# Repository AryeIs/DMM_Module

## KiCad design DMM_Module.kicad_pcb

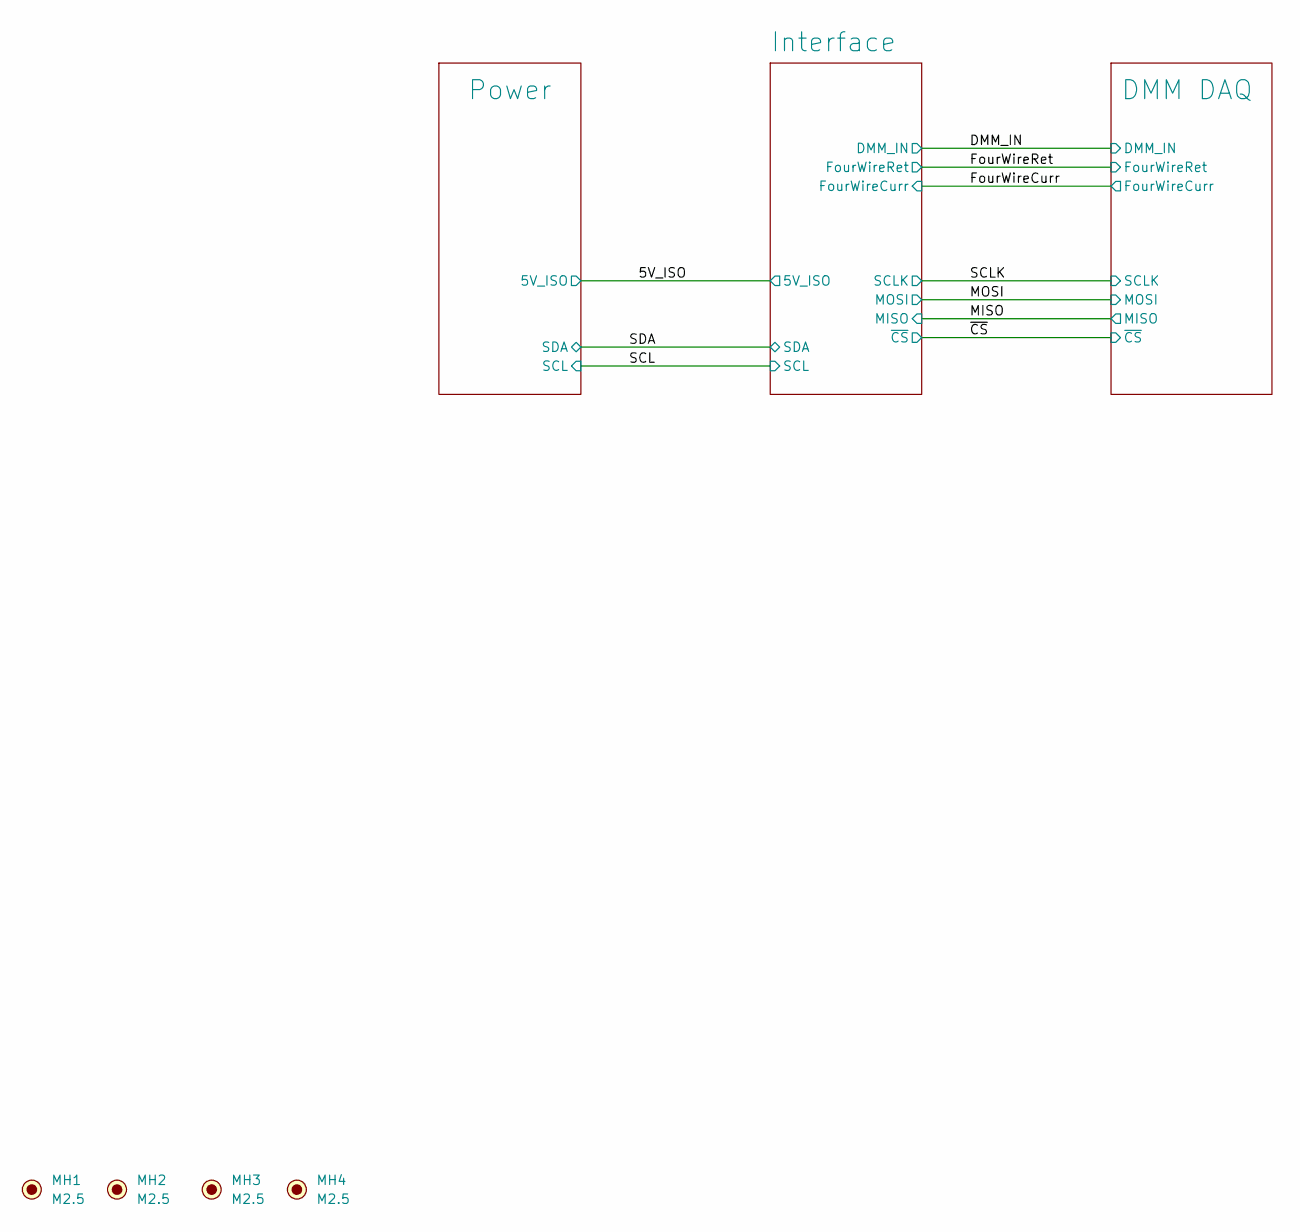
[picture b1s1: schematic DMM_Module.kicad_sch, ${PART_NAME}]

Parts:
MH1, MH2, MH3, MH4: M2.5; MountingHole_2.7mm_M2.5

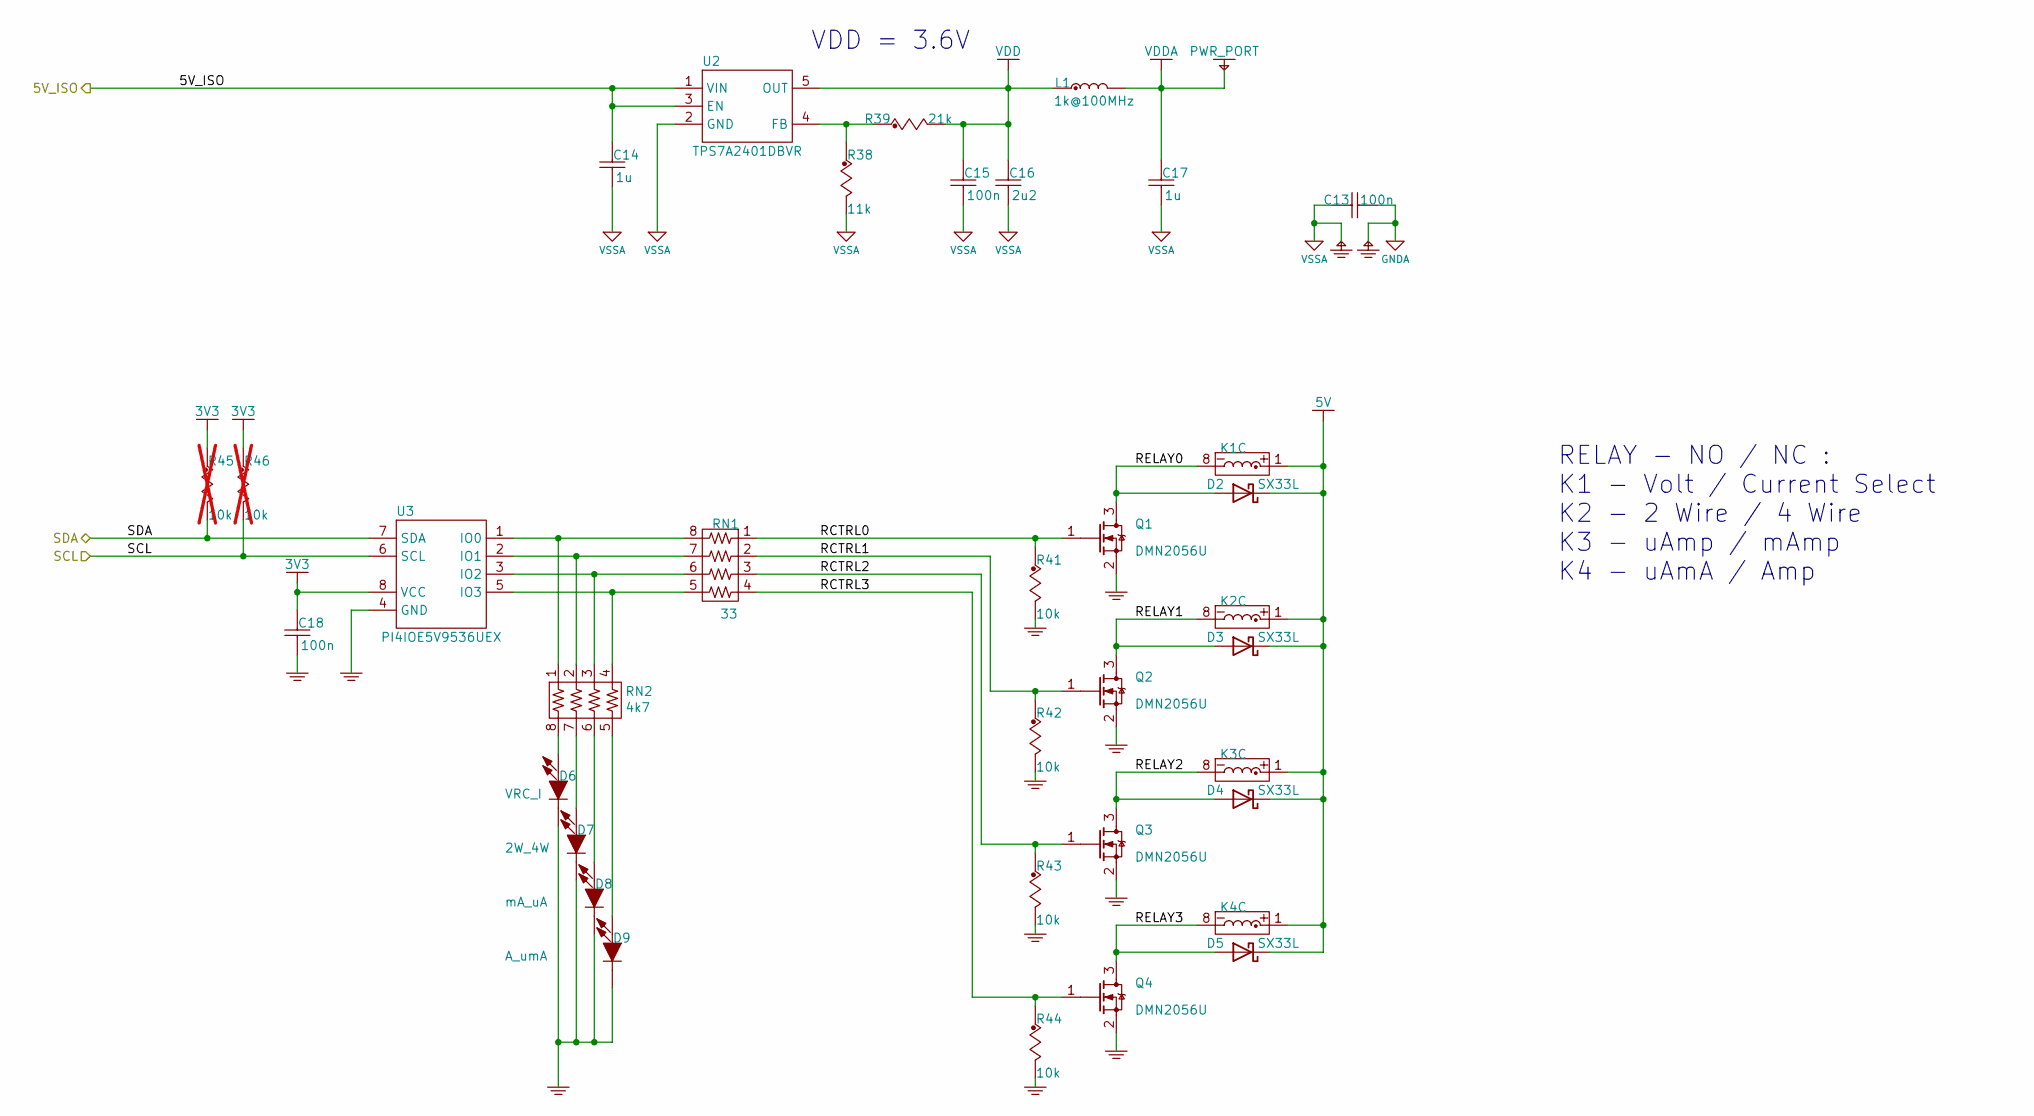
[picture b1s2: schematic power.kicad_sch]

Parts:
C13, C15, C18: 100n; C_0603_1608Metric; Voltage 50V; MFG PN CL10B104JB8NNNC
C14, C17: 1u; C_0603_1608Metric; Voltage 25V; MFG PN CL10B105KA8NNNC
C16: 2u2; C_0603_1608Metric; Voltage 25V; MFG PN CL10A225KP8NNNC
D2, D3, D4, D5: SX33L; D_SOD-123; MFG PN MBR1020VL_R1_00001
D6: VRC_I; LED_0603_1608Metric; MFG PN 150060GS55040
D7: 2W_4W; LED_0603_1608Metric; MFG PN 150060GS55040
D8: mA_uA; LED_0603_1608Metric; MFG PN 150060GS55040
D9: A_umA; LED_0603_1608Metric; MFG PN 150060GS55040
K1, K2, K3, K4: G6K-2F-Y-TR; DPDT_G6K-2F-Y; Voltage 5VDC; MFG PN G6K-2F-Y-TR DC5
L1: 1k@100MHz; L_0603_1608Metric; MFG PN 74279266
Q1, Q2, Q3, Q4: DMN2056U; SOT-23; MFG PN DMN2056U-7
R38: 11k; R_0603_1608Metric; Tolerance 1%; MFG PN CR0603-FX-1102ELF
R39: 21k; R_0603_1608Metric; Tolerance 1%; MFG PN CR0603-FX-2102ELF
R41, R42, R43, R44: 10k; R_0603_1608Metric; Tolerance 1%; MFG PN CR0603AFX-1002EAS
R45, R46: 10k; R_0603_1608Metric; Tolerance 1%; MFG PN CR0603AFX-1002EAS; not fitted
RN1: 33; R_Array_Convex_4x0603; MFG PN YC164-FR-0733RL
RN2: 4k7; R_Array_Convex_4x0603; MFG PN YC164-FR-074K7L
U2: TPS7A2401DBVR; SOT-23-5; MFG PN TPS7A2401DBVR
U3: PI4IOE5V9536UEX; TSSOP-8_3x3mm_P0.65mm; MFG PN PI4IOE5V9536UEX

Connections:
3V3: C18.2, R45.1, R46.1, U3.8 (VCC); also elsewhere on the board
5V: D2.1 (K), D3.1 (K), D4.1 (K), D5.1 (K), K1.1 (COIL1), K2.1 (COIL1), K3.1 (COIL1), K4.1 (COIL1); also elsewhere on the board
/5V_ISO: C14.2, U2.1 (VIN), U2.3 (EN); also elsewhere on the board
/Power/RCTRL0: Q1.1 (G), R41.1, RN1.1
/Power/RCTRL1: Q2.1 (G), R42.1, RN1.2
/Power/RCTRL2: Q3.1 (G), R43.1, RN1.3
/Power/RCTRL3: Q4.1 (G), R44.1, RN1.4
/Power/RELAY0: D2.2 (A), K1.8 (COIL2), Q1.3 (D)
/Power/RELAY1: D3.2 (A), K2.8 (COIL2), Q2.3 (D)
/Power/RELAY2: D4.2 (A), K3.8 (COIL2), Q3.3 (D)
/Power/RELAY3: D5.2 (A), K4.8 (COIL2), Q4.3 (D)
/SCL: R46.2, U3.6 (SCL); also elsewhere on the board
/SDA: R45.2, U3.7 (SDA); also elsewhere on the board
GND: C18.1, D6.1 (K), D7.1 (K), D8.1 (K), D9.1 (K), Q1.2 (S), Q2.2 (S), Q3.2 (S), Q4.2 (S), R41.2, R42.2, R43.2, R44.2, U3.4 (GND); also elsewhere on the board
unnamed: D6.2 (A), RN2.8
unnamed: D7.2 (A), RN2.7
unnamed: D8.2 (A), RN2.6
unnamed: D9.2 (A), RN2.5
unnamed: R38.1, R39.1, U2.4 (FB)
unnamed: RN1.8, RN2.1, U3.1 (IO0)
unnamed: RN1.7, RN2.2, U3.2 (IO1)
unnamed: RN1.6, RN2.3, U3.3 (IO2)
unnamed: RN1.5, RN2.4, U3.5 (IO3)
VDD: C15.2, C16.2, L1.1, R39.2, U2.5 (OUT); also elsewhere on the board
VDDA: C17.2, L1.2; also elsewhere on the board

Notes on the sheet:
RELAY - NO / NC : K1 - Volt / Current Select K2 - 2 Wire / 4 Wire K3 - uAmp / mAmp K4 - uAmA / Amp
VDD = 3.6V

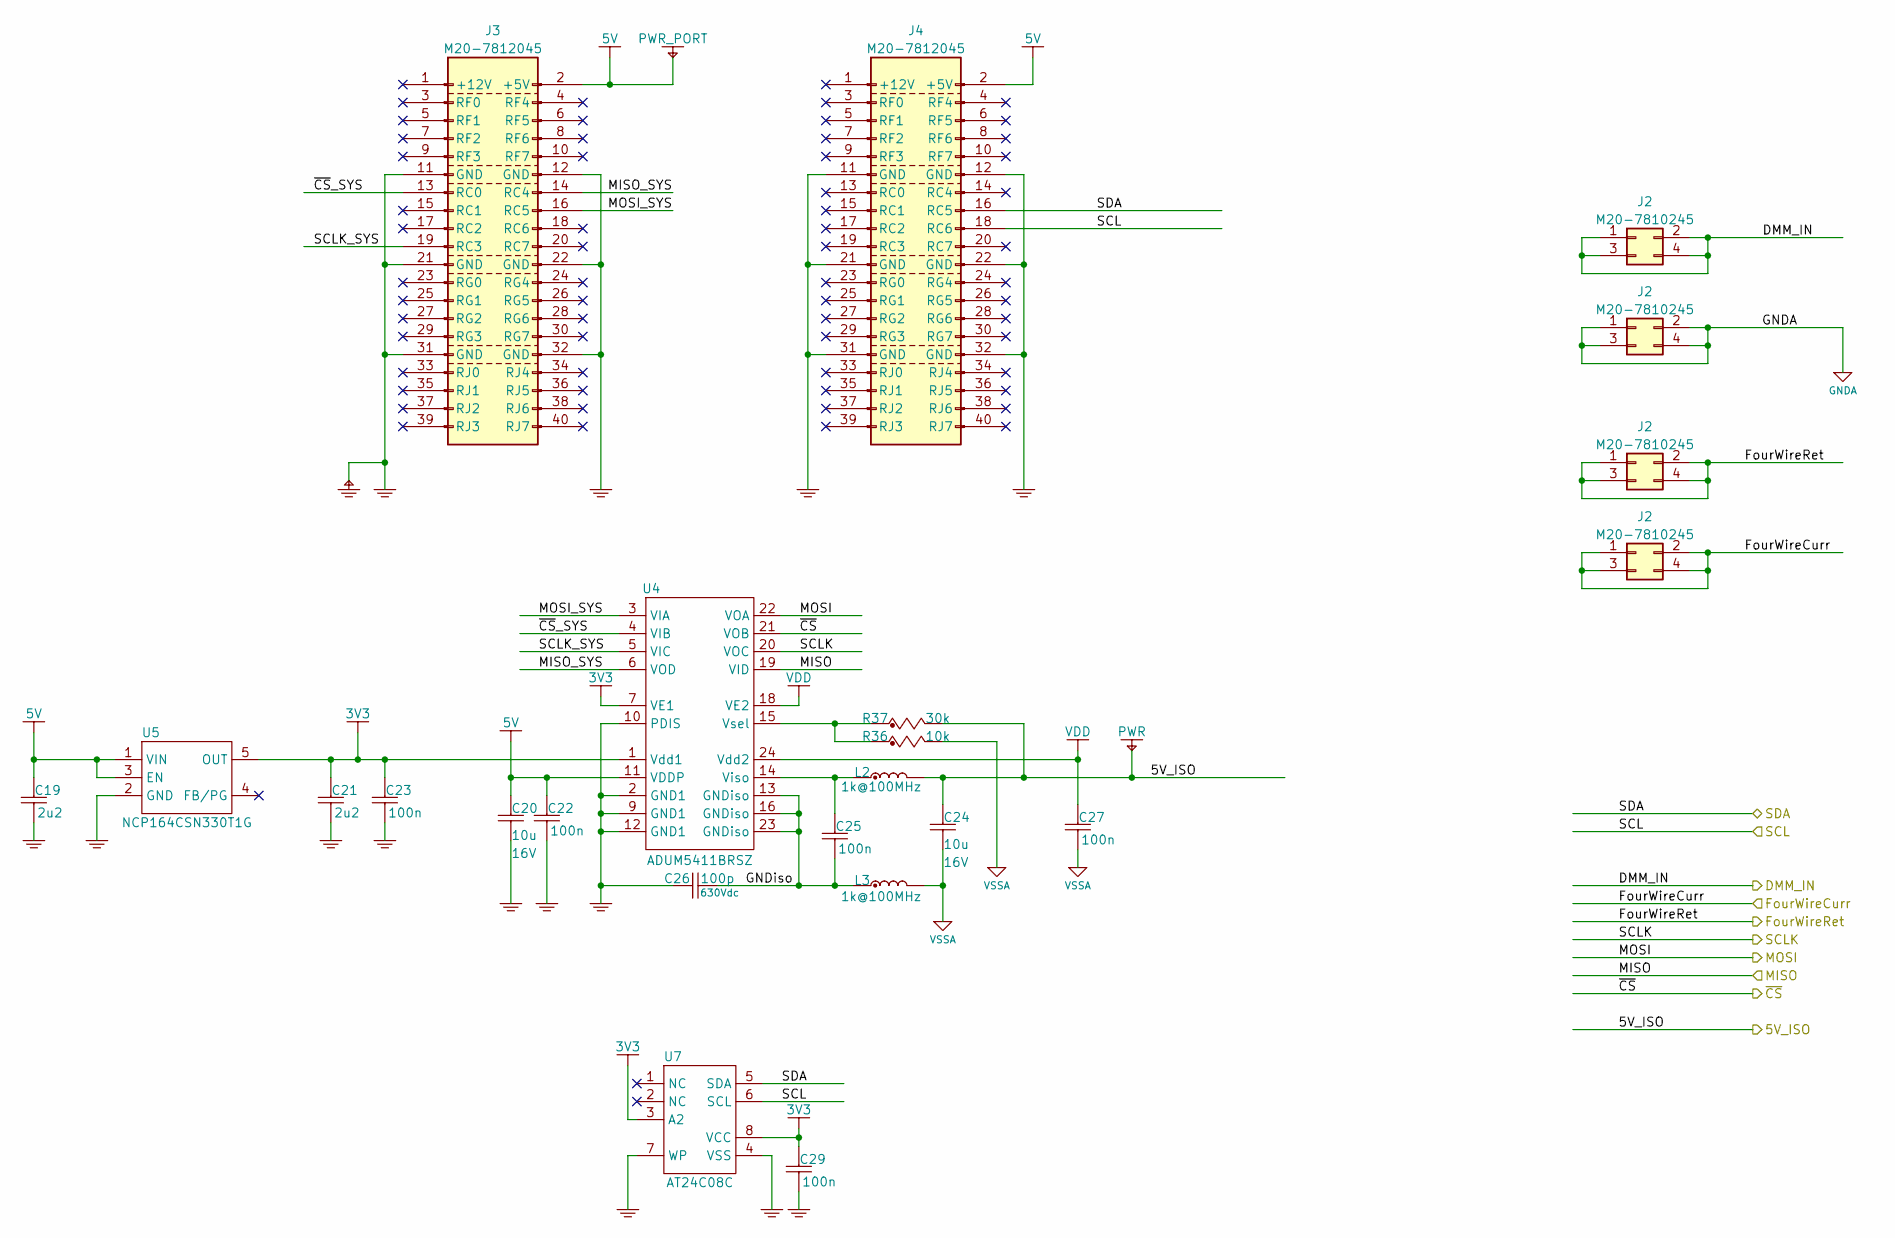
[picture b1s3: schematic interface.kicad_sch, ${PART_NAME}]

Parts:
C19, C21: 2u2; C_0603_1608Metric; Voltage 25V; MFG PN CL10A225KP8NNNC
C20, C24: 10u; C_0603_1608Metric; Voltage 16V; MFG PN CL10A106KO8NQNC
C22, C23, C25, C27, C29: 100n; C_0603_1608Metric; Voltage 50V; MFG PN CL10B104JB8NNNC
C26: 100p; C_1206_3216Metric; Voltage 630Vdc; Tolerance 5%; MFG PN CC1206JKNPOZBN101
J2: M20-7810245; Header_SKT_02x02_Fixed_Harwin_M20-7810245; Mfg P/N M20-7810245
J3, J4: M20-7812045; Header_SKT_02x20_Fixed_Harwin_M20-7812045; Mfg P/N M20-7812045
L2, L3: 1k@100MHz; L_0603_1608Metric; MFG PN 74279266
R36: 10k; R_0603_1608Metric; Tolerance 1%; MFG PN CR0603AFX-1002EAS
R37: 30k; R_0603_1608Metric; Tolerance 1%; MFG PN CR0603-FX-3002ELF
U4: ADUM5411BRSZ; SSOP-24_5.3x8.2mm_P0.65mm; MFG PN ADUM5411BRSZ-RL7
U5: NCP164CSN330T1G; SOT-23-5; MFG PN NCP164CSN330T1G
U7: AT24C08C; TSSOP-8_4.4x3mm_P0.65mm; MFG PN AT24C08C-XHM-T

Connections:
3V3: C21.2, C23.2, C29.2, U4.1 (Vdd1), U4.7 (VE1), U5.5 (OUT), U7.3 (A2), U7.8 (VCC); also elsewhere on the board
5V: C19.2, C20.2, C22.2, J3.2 (+5V), J4.2 (+5V), U4.11 (VDDP), U5.1 (VIN), U5.3 (EN); also elsewhere on the board
/5V_ISO: C24.2, L2.2, R37.2; also elsewhere on the board
/Interface/GNDiso: C25.1, C26.1, L3.1, U4.13 (GNDiso), U4.16 (GNDiso), U4.23 (GNDiso)
/Interface/MISO_SYS: J3.14 (RC4), U4.6 (VOD)
/Interface/MOSI_SYS: J3.16 (RC5), U4.3 (VIA)
/Interface/SCLK_SYS: J3.19 (RC3), U4.5 (VIC)
/Interface/~CS_SYS: J3.13 (RC0), U4.4 (VIB)
/MISO: U4.19 (VID); also elsewhere on the board
/MOSI: U4.22 (VOA); also elsewhere on the board
/SCL: J4.18 (RC6), U7.6 (SCL); also elsewhere on the board
/SCLK: U4.20 (VOC); also elsewhere on the board
/SDA: J4.16 (RC5), U7.5 (SDA); also elsewhere on the board
/~CS: U4.21 (VOB); also elsewhere on the board
GND: C19.1, C20.1, C21.1, C22.1, C23.1, C26.2, C29.1, J3.11 (GND), J3.12 (GND), J3.21 (GND), J3.22 (GND), J3.31 (GND), J3.32 (GND), J4.11 (GND), J4.12 (GND), J4.21 (GND), J4.22 (GND), J4.31 (GND), J4.32 (GND), U4.2 (GND1), U4.9 (GND1), U4.10 (PDIS), U4.12 (GND1), U5.2 (GND), U7.4 (VSS), U7.7 (WP); also elsewhere on the board
unnamed: C25.2, L2.1, U4.14 (Viso)
unnamed: R36.1, R37.1, U4.15 (Vsel)
VDD: C27.2, U4.18 (VE2), U4.24 (Vdd2); also elsewhere on the board

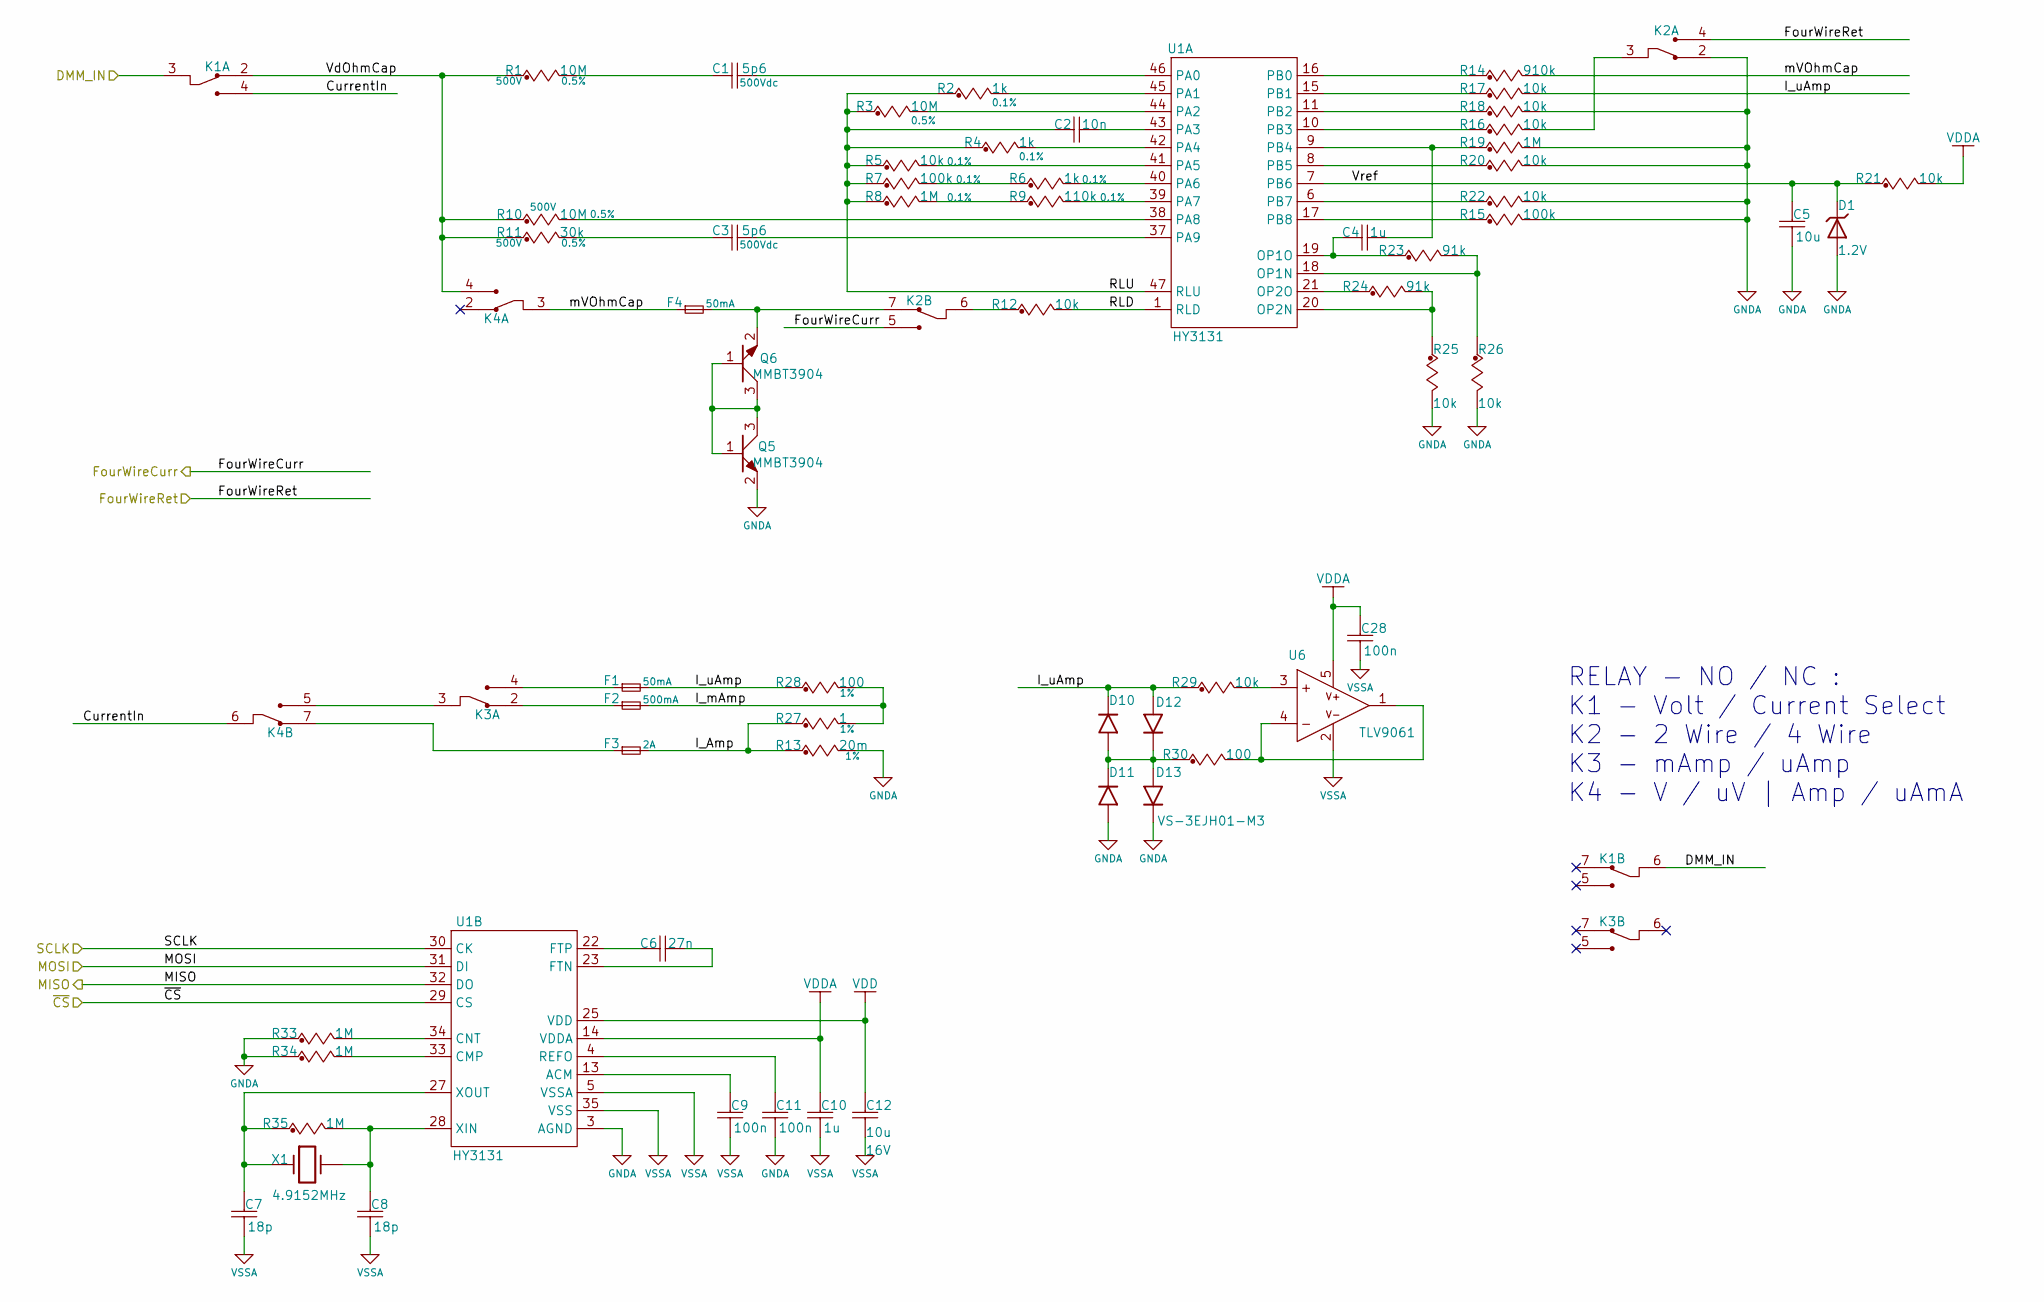
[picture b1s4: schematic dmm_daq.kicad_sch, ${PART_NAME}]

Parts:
C1, C3: 5p6; C_1206_3216Metric; Voltage 500Vdc; Tolerance 5%; MFG PN CC1206CRNPOBBN5R6
C2: 10n; C_0603_1608Metric; Voltage 50V; MFG PN CL10B103KB8NNNC
C4, C10: 1u; C_0603_1608Metric; Voltage 25V; MFG PN CL10B105KA8NNNC
C5: 10u; C_0603_1608Metric; Voltage 10V; MFG PN CL10A106KP8NNWC
C6: 27n; C_0603_1608Metric; Voltage 50V; MFG PN CC0603JRX7R9BB273
C7, C8: 18p; C_0603_1608Metric; Voltage 50V; MFG PN CL10C180JB81PNC
C9, C11, C28: 100n; C_0603_1608Metric; Voltage 50V; MFG PN CL10B104JB8NNNC
C12: 10u; C_0603_1608Metric; Voltage 16V; MFG PN CL10A106KO8NQNC
D1: 1.2V; SOT-23; MFG PN LM385M3X-1.2/NOPB
D10, D11, D12, D13: VS-3EJH01-M3; SlimSMPA; MFG PN VS-3EJH01-M3/6B
F1, F4: 50mA; Fuse_1206_3216Metric; MFG PN 0ZCJ0005FF2E
F2: 500mA; Fuse_1206_3216Metric; MFG PN 0ZCJ0050AF2E
F3: 2A; Fuse_1206_3216Metric; MFG PN 0ZCJ0200FF2C
K1, K2, K3, K4: G6K-2F-Y-TR; DPDT_G6K-2F-Y; Voltage 5VDC; MFG PN G6K-2F-Y-TR DC5
Q5, Q6: MMBT3904; SOT-23-3; MFG PN MMBT3904
R1, R10: 10M; R_1206_3216Metric; Tolerance 0.5%; Voltage 500V; MFG PN ERJ-P08D1004V
R2, R4, R6: 1k; R_0603_1608Metric; Tolerance 0.1%; MFG PN ERJ-PB3B1001V
R3: 10M; R_0603_1608Metric; Tolerance 0.5%; MFG PN CRCW060310M0DHEAP
R5: 10k; R_0603_1608Metric; Tolerance 0.1%; MFG PN ERA-3VEB1002V
R7: 100k; R_0603_1608Metric; Tolerance 0.1%; MFG PN ERA-3VEB1003V
R8, R19, R33, R34, R35: 1M; R_0603_1608Metric; Tolerance 0.1%; MFG PN RT0603BRD071ML
R9: 110k; R_0603_1608Metric; Tolerance 0.1%; MFG PN ERA-3AEB114V
R11: 30k; R_1206_3216Metric; Tolerance 0.5%; Voltage 500V; MFG PN ERJ-P08D3002V
R12, R16, R17, R18, R20, R21, R22, R25, R26, R29: 10k; R_0603_1608Metric; Tolerance 1%; MFG PN CR0603AFX-1002EAS
R13: 20m; R_1206_3216Metric; Tolerance 1%; MFG PN ERJ-8CWFR020V
R14: 910k; R_0603_1608Metric; Tolerance 1%; MFG PN CRCW0603910KFKEA
R15: 100k; R_0603_1608Metric; Tolerance 1%; MFG PN CR0603-FX-1003ELF
R23, R24: 91k; R_0603_1608Metric; Tolerance 1%; MFG PN CR0603-FX-9102ELF
R27: 1; R_1206_3216Metric; Tolerance 1%; MFG PN ERJ-8BQF1R0V
R28: 100; R_1206_3216Metric; Tolerance 1%; MFG PN RT1206FRD07100RL
R30: 100; R_0603_1608Metric; Tolerance 1%; MFG PN CR0603-FX-1000ELF
U1: HY3131; LQFP-48_7x7mm_P0.5mm; MFG PN HY3131-L048
U6: TLV9061; SOT-23-5; MFG PN TLV9061QDBVRQ1
X1: 4.9152MHz; Crystal_SMD_HC49-SD; MFG PN ABLS-4.9152MHZ-B4-T

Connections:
/DMM DAQ/CurrentIn: K1.4 (NO1), K4.6 (COM2)
/DMM DAQ/I_Amp: F3.2, R13.1, R27.1
/DMM DAQ/I_mAmp: F2.2, R27.2, R28.2
/DMM DAQ/I_uAmp: D10.1 (K), D12.2 (A), F1.2, R17.2, R28.1, R29.1
/DMM DAQ/RLD: R12.2, U1.1 (RLD)
/DMM DAQ/RLU: C2.2, R2.1, R3.1, R4.1, R5.1, R7.1, R8.1, U1.47 (RLU)
/DMM DAQ/VdOhmCap: K1.2 (NC1), K4.4 (NO1), R1.1, R10.1, R11.1
/DMM DAQ/Vref: C5.2, D1.1 (K), R21.1, U1.7 (PB6)
/DMM DAQ/mVOhmCap: F4.1, K4.3 (COM1), R14.2
/DMM_IN: K1.3 (COM1), K1.6 (COM2); also elsewhere on the board
/FourWireCurr: K2.5 (NO2); also elsewhere on the board
/FourWireRet: K2.4 (NO1); also elsewhere on the board
/MISO: U1.32 (DO); also elsewhere on the board
/MOSI: U1.31 (DI); also elsewhere on the board
/SCLK: U1.30 (CK); also elsewhere on the board
/~CS: U1.29 (CS); also elsewhere on the board
unnamed: C1.2, R1.2
unnamed: C3.2, R11.2
unnamed: D10.2 (A), D11.1 (K), D12.1 (K), D13.2 (A), R30.1
unnamed: K2.3 (COM1), R16.2
unnamed: K2.6 (COM2), R12.1
unnamed: F4.2, K2.7 (NC2), Q6.2 (S)
unnamed: K3.3 (COM1), K4.5 (NO2)
unnamed: F2.1, K3.2 (NC1)
unnamed: F1.1, K3.4 (NO1)
unnamed: F3.1, K4.7 (NC2)
unnamed: Q5.1 (G), Q5.3 (D), Q6.1 (G), Q6.3 (D)
unnamed: R6.1, R7.2
unnamed: R8.2, R9.1
unnamed: R23.2, R26.1, U1.18 (OP1N)
unnamed: C4.2, R23.1, U1.19 (OP1O)
unnamed: R24.2, R25.1, U1.20 (OP2N)
unnamed: R24.1, U1.21 (OP2O)
unnamed: C1.1, U1.46 (PA0)
unnamed: R2.2, U1.45 (PA1)
unnamed: R3.2, U1.44 (PA2)
unnamed: C2.1, U1.43 (PA3)
unnamed: R4.2, U1.42 (PA4)
unnamed: R5.2, U1.41 (PA5)
unnamed: R6.2, U1.40 (PA6)
unnamed: R9.2, U1.39 (PA7)
unnamed: R10.2, U1.38 (PA8)
unnamed: C3.1, U1.37 (PA9)
unnamed: R14.1, U1.16 (PB0)
unnamed: R17.1, U1.15 (PB1)
unnamed: R18.1, U1.11 (PB2)
unnamed: R16.1, U1.10 (PB3)
unnamed: C4.1, R19.1, U1.9 (PB4)
unnamed: R20.1, U1.8 (PB5)
unnamed: R22.1, U1.6 (PB7)
unnamed: R15.1, U1.17 (PB8)
unnamed: C9.2, U1.13 (ACM)
unnamed: R34.2, U1.33 (CMP)
unnamed: R33.2, U1.34 (CNT)
unnamed: C6.1, U1.23 (FTN)
unnamed: C6.2, U1.22 (FTP)
unnamed: C11.2, U1.4 (REFO)
unnamed: C8.2, R35.2, U1.28 (XIN), X1.2
unnamed: C7.2, R35.1, U1.27 (XOUT), X1.1
unnamed: R29.2, U6.3 (IN+)
unnamed: R30.2, U6.1 (OUTA), U6.4 (IN-)
VDD: C12.2, U1.25 (VDD); also elsewhere on the board
VDDA: C10.2, C28.2, R21.2, U1.14 (VDDA), U6.5 (V+); also elsewhere on the board

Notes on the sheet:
RELAY - NO / NC : K1 - Volt / Current Select K2 - 2 Wire / 4 Wire K3 - mAmp / uAmp K4 - V / uV | Amp / uAmA

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
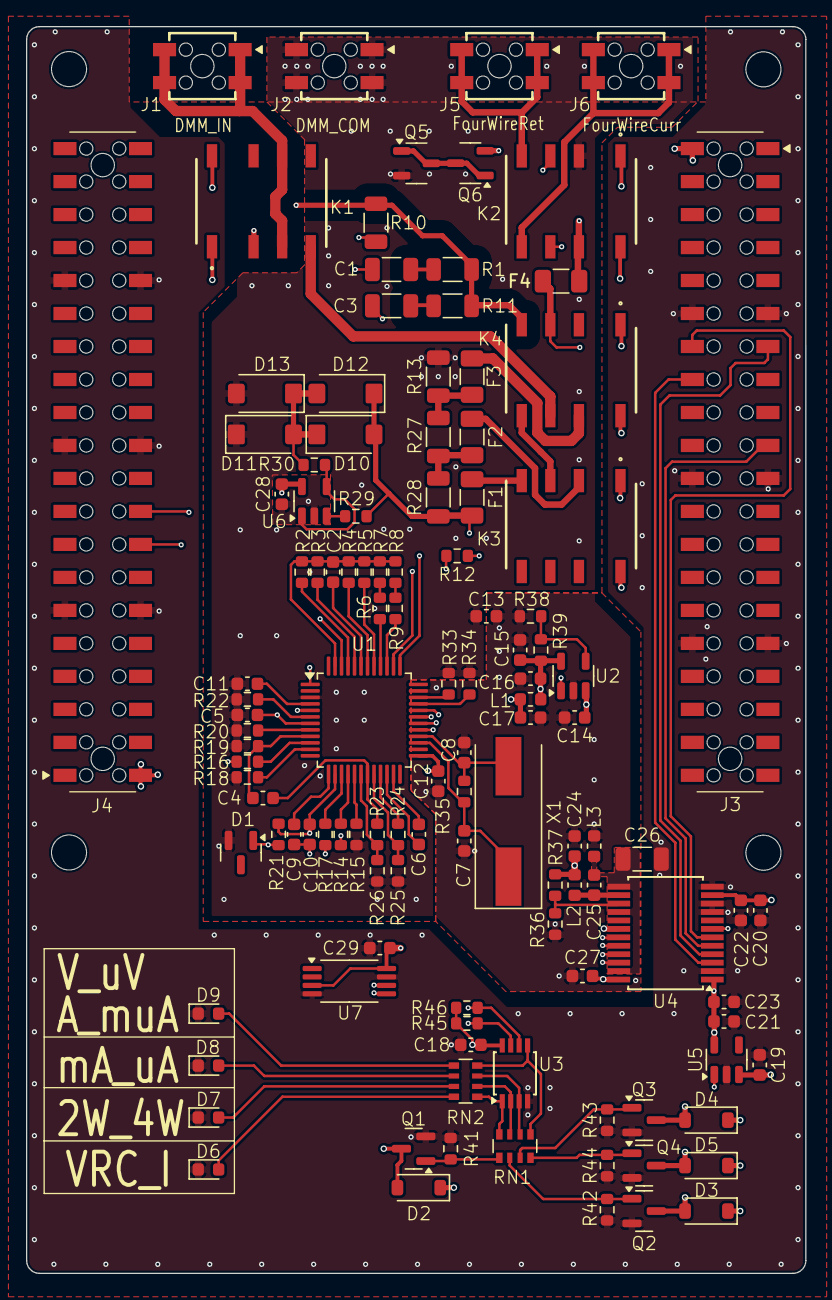
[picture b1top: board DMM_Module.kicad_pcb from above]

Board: 4 copper layers, 60.0 x 96.0 mm, 122 parts (0 on the bottom side), 95 nets.

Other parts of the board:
J1, J5, J6: M20-7810245; Header_SKT_02x02_Fixed_Harwin_M20-7810245

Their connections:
/DMM_IN: J1.1, J1.2, J1.3, J1.4; also elsewhere on the board
/FourWireCurr: J6.1, J6.2, J6.3, J6.4; also elsewhere on the board
/FourWireRet: J5.1, J5.2, J5.3, J5.4; also elsewhere on the board

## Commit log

2024-02-04 preliminary placement
2024-02-18 Board is fully routed
2024-02-20 Step and gerber files added
2024-02-20 Drills added
2024-02-20 Drills added, gitignore updated
2024-04-19 Added galvanic isolation
2024-04-19 Board thickness adjusted
2024-04-22 Schematics updated with current protection and EEPROM
2024-04-25 Isolated analog path is fully routed
2024-04-26 Added GND vias for high current path
2024-04-26 Relay traces were aligned
2024-04-26 Gerber archive updated
2024-04-27 U1 pad thickness was reduced to 0.28 to comply with the manufacturer's constraints
2024-06-17 10MOhm resistors partnumber updated
